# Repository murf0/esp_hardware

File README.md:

# esp_hardware
This is the hardware file for thebutton. Misusing components i had at the time, Totally untested.

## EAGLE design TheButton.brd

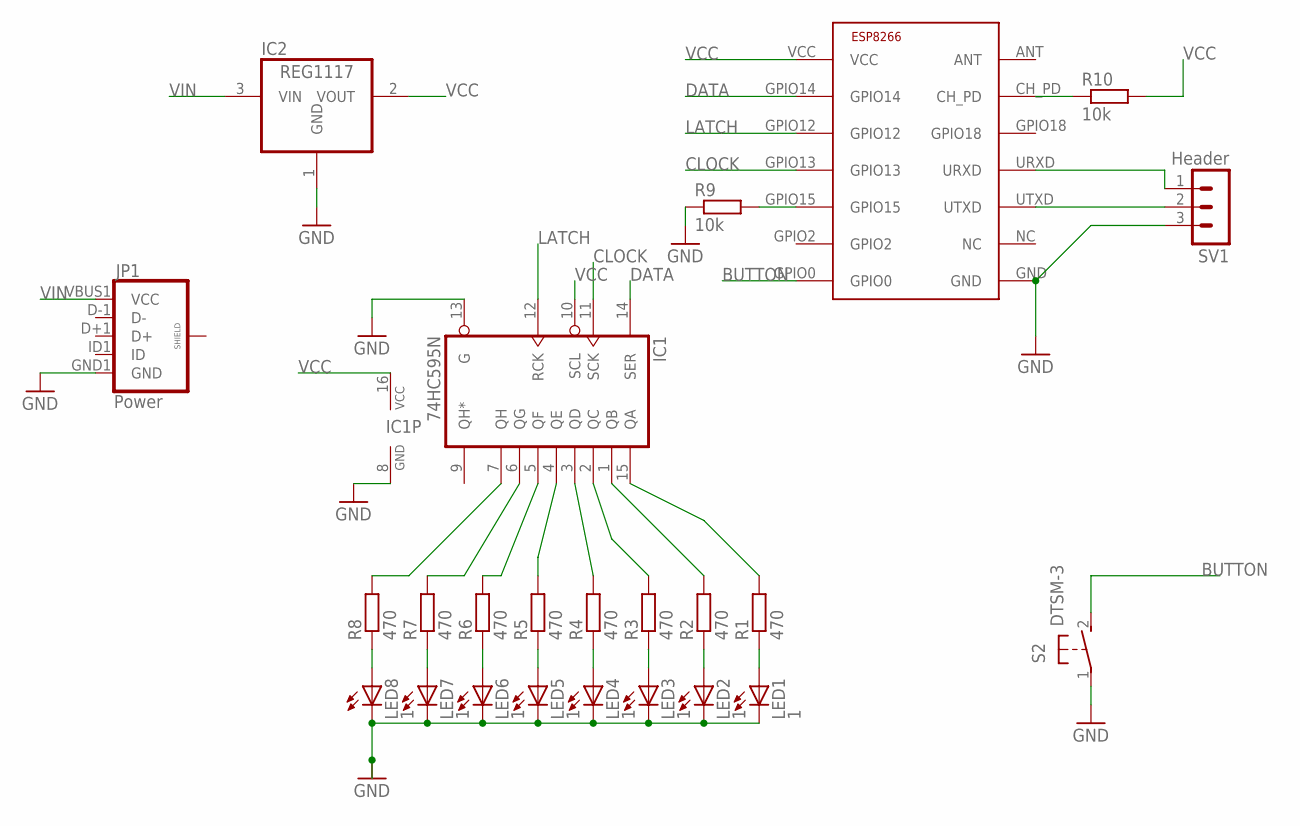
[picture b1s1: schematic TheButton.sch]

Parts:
IC1: 74HC595N; DIL16
IC2: REG1117; SOT223
JP1: Power; USB-B-MICRO-SMD_V03
LED1, LED2, LED3, LED4, LED5, LED6, LED7, LED8: 1; LED3MM
R1, R2, R3, R4, R5, R6, R7, R8: 470; 0204/7
R9, R10: 10k; 0204/5
S2: DTSM-3
SV1: Header; MA03-1
U$1: ESP8266; ESP-03

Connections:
10KLOW: R9.2, U$1.GPIO15
BUTTON: S2.2, U$1.GPIO0
CLOCK: IC1.11 (SCK), U$1.GPIO13
DATA: IC1.14 (SER), U$1.GPIO14
GND: IC1.8 (GND), IC1.13 (G), IC2.1 (GND), JP1.GND1 (GND), LED1.K (C), LED2.K (C), LED3.K (C), LED4.K (C), LED5.K (C), LED6.K (C), LED7.K (C), LED8.K (C), R9.1, S2.1, SV1.3, U$1.GND
LATCH: IC1.12 (RCK), U$1.GPIO12
unnamed: LED1.A, R1.1
unnamed: LED8.A, R8.1
unnamed: LED7.A, R7.1
unnamed: LED6.A, R6.1
unnamed: LED5.A, R5.1
unnamed: LED4.A, R4.1
unnamed: LED3.A, R3.1
unnamed: LED2.A, R2.1
unnamed: IC1.15 (QA), R1.2
unnamed: IC1.1 (QB), R2.2
unnamed: IC1.2 (QC), R3.2
unnamed: IC1.3 (QD), R4.2
unnamed: IC1.4 (QE), R5.2
unnamed: R10.1, U$1.CH_PD
unnamed: IC1.5 (QF), R6.2
unnamed: IC1.6 (QG), R7.2
unnamed: IC1.7 (QH), R8.2
unnamed: SV1.1, U$1.URXD
unnamed: SV1.2, U$1.UTXD
VCC: IC1.10 (SCL), IC1.16 (VCC), IC2.2 (VOUT), R10.2, U$1.VCC
VIN: IC2.3 (VIN), JP1.VBUS1 (VCC)

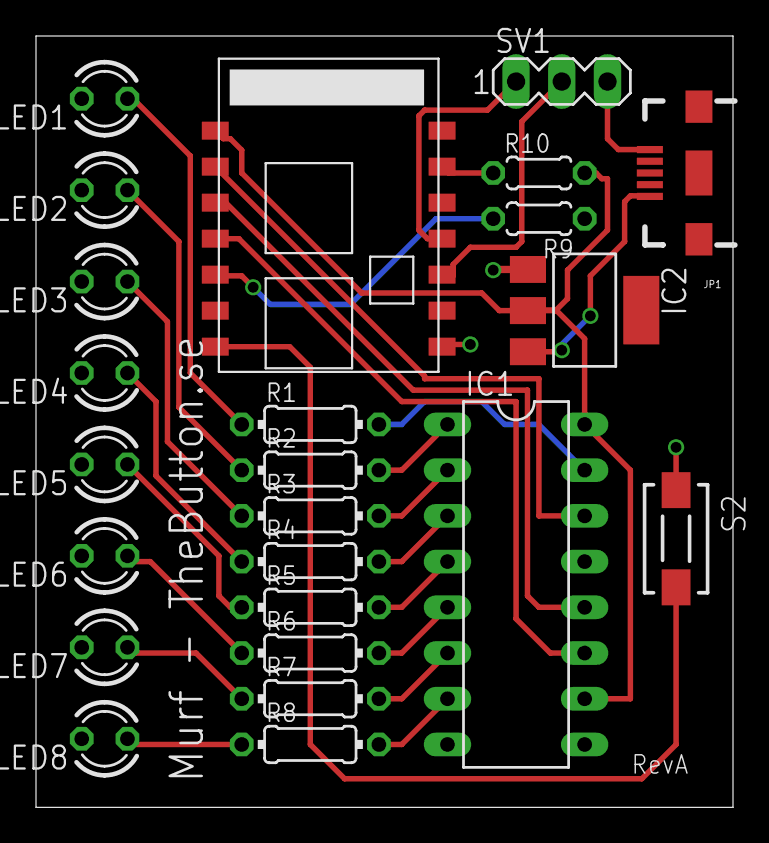
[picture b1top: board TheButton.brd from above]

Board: 2 copper layers, 38.7 x 42.9 mm, 24 parts (0 on the bottom side), 27 nets.

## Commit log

2015-04-08 First commit, Alpha 1 board.
2015-04-08 Added png Changed USB-contat to SMD only version
2015-04-08 Added image
2015-04-08 this time, file will be visible
